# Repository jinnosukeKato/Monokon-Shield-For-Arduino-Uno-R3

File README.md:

# Monokon-Shield for Arduino Uno R3

ものづくりコンテスト制御の対象基板、制作基盤と Arduino Uno R3 を接続するためのシールドです

[KiCad 6.0](https://www.kicad.org/) 用のデータです  
ガーバーファイルとドリルファイルを出力して、基板メーカ等に発注するなりしてください

## 特徴

- Arduino Uno R3 と同寸法
- デバッグ用LED搭載
- 一層基板

## 使いかた

この基盤をArduino Unoに差し込み、CN3に制作基盤(当日制作する基板)を接続し、CN1, CN2に制御対象基板を接続してください。

## 必要な部品

- [330Ω 抵抗器](https://akizukidenshi.com/catalog/g/gR-25331/) x3
- [10kΩ 抵抗器](https://akizukidenshi.com/catalog/g/gR-25103/) x3
- [C1815 トランジスタ](https://akizukidenshi.com/catalog/g/gI-06475/) x3
- [お好きな色のLED](https://akizukidenshi.com/catalog/g/gI-11333/) x3
- [10ピン ボックスヘッダ](https://akizukidenshi.com/catalog/g/gC-12664/) x2
- [2.54mm ピンヘッダ](https://akizukidenshi.com/catalog/g/gC-00167/)

## 組み立て上の注意点

- ランドが少し小さいです
- J1-4はピンが裏を向くように実装してください
- トランジスタの足は、ランドに適切に刺さるよう曲げてください
- CN1, CN2のフラットケーブルが交差してしまう配線になっています
- CN1, CN2が参考画像では10ピンヘッダになっていますが、ボックスヘッダを実装することをオススメします
- CN1, CN2にボックスヘッダを実装する場合は▼がLED側に来るように実装してください
- シルクに`神奈川工業高校 ものづくり同好会`と入ってます

## ピン対応表

| Arduinoのピン | 接続先 | メモ |
| --- | --- | --- |
| 0 | NC | - |
| 1 | NC | - |
| 2 | 7セグ左ON/OFF | - |
| 3 | 7セグ右ON/OFF | - |
| 4 | ブザー | tone()で鳴らしてください |
| 5 | クロック | DCモーター/ステッピングモーター使用時に入力必須 |
| 6 | 7セグ/ステッピング | 7セグのピンは一番上の横棒から時計回り |
| 7 | 7セグ/ステッピング | - |
| 8 | 7セグ/ステッピング | - |
| 9 | 7セグ/ステッピング | - |
| 10 | 7セグ/DCモーター | - |
| 11 | 7セグ/DCモーター | - |
| 12 | 7セグ | 中央横棒 |
| 13 | 7セグ | 小数点 |
| 14 | 製作基盤入力 | digitalRead用 |
| 15 | 製作基盤入力 | digitalRead用 |
| 16 | 製作基盤入力 | digitalRead用 |
| A0 | 製作基盤入力 | AnalogRead用 |
| A1 | 製作基盤入力 | AnalogRead用 |
| A2 | 製作基盤入力 | AnalogRead用 |

## Special Thanks

- K先輩(Arduino MEGA用の基盤データ提供、LEDの回路を参考にさせてもらいました)
- 神奈川工業高校ものづくり同好会

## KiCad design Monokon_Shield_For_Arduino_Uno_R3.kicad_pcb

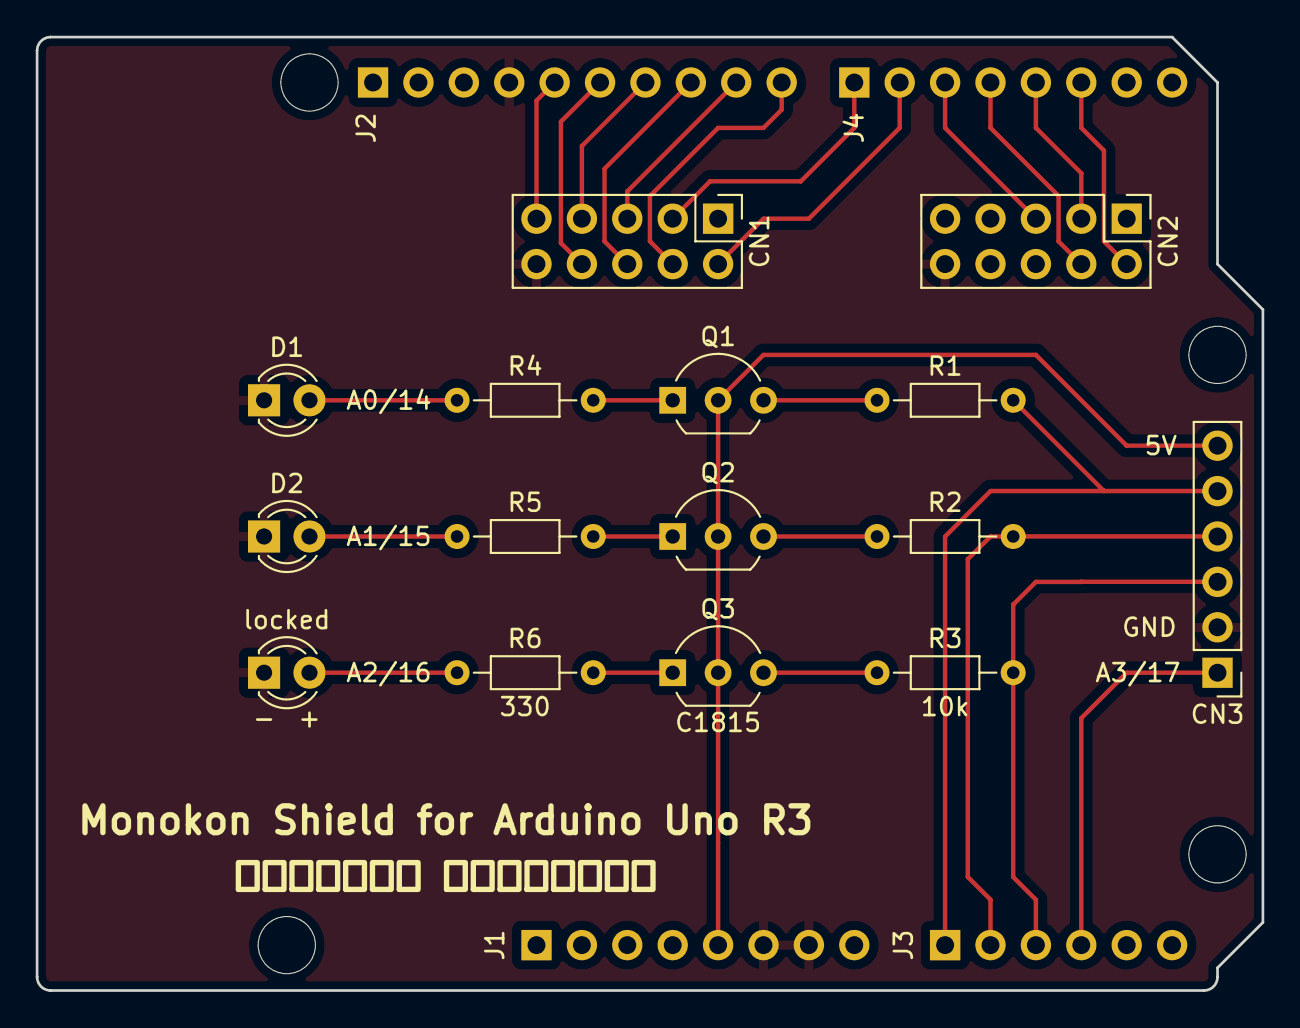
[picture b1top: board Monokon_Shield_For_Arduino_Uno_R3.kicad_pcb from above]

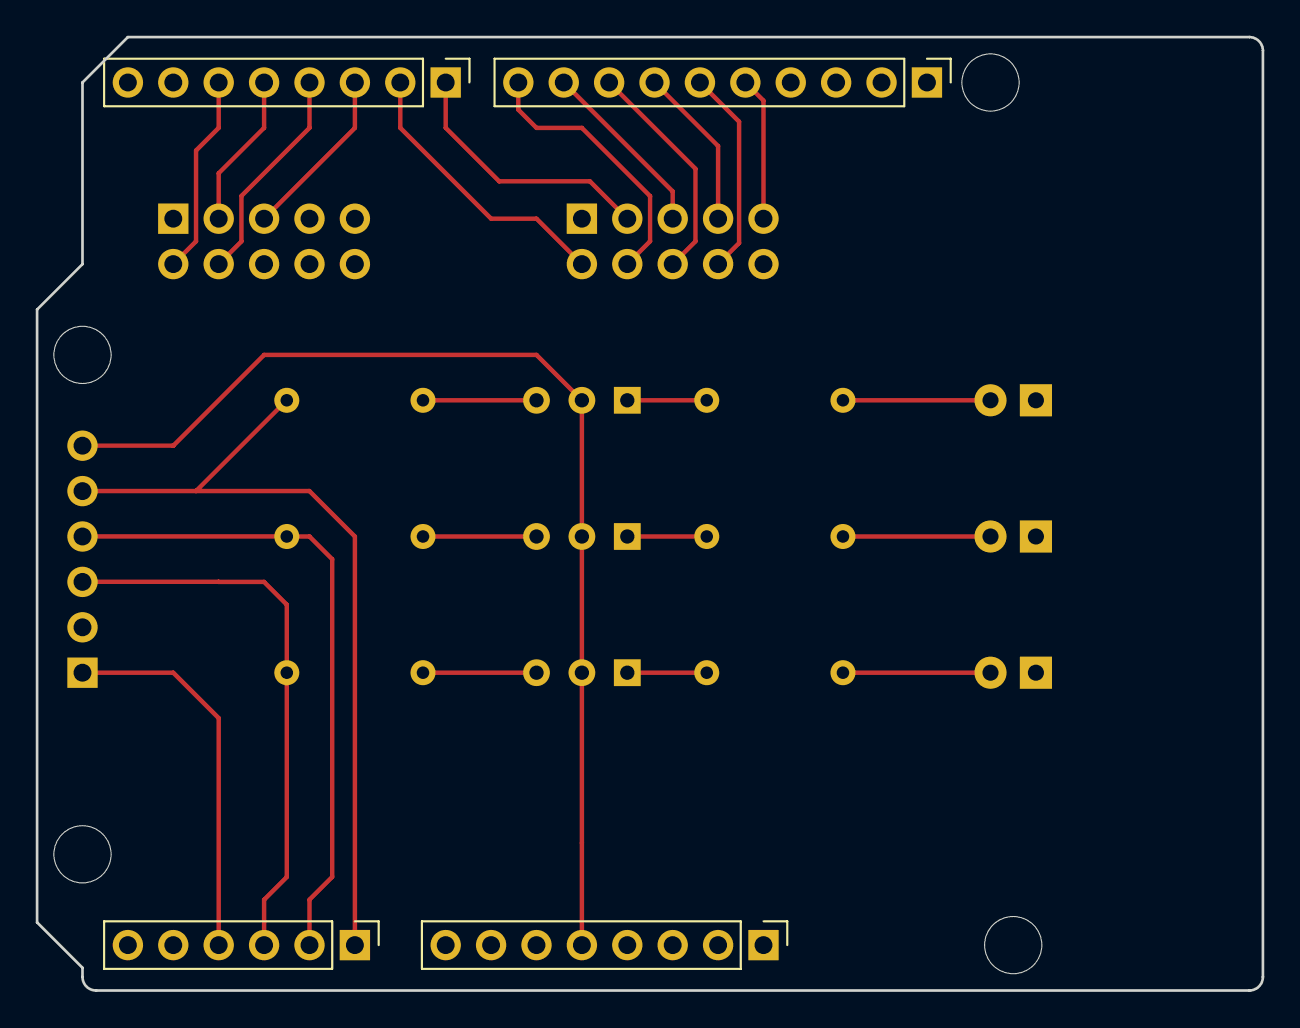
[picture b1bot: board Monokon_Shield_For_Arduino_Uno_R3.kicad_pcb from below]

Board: 2 copper layers, 68.6 x 53.3 mm, 23 parts (4 on the bottom side), 27 nets.

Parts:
CN1, CN2: 2x5 10-Pin Male Box Header; PinHeader_2x05_P2.54mm_Vertical
CN3: 6-Pin Headers; PinHeader_1x06_P2.54mm_Vertical
D1, D2: LED; LED_D3.0mm
J1: locked; PinHeader_1x08_P2.54mm_Vertical
J2: Digital/PWM; PinHeader_1x10_P2.54mm_Vertical
J3: Analog; PinHeader_1x06_P2.54mm_Vertical
J4: Digital/PWM; PinHeader_1x08_P2.54mm_Vertical
MH1, MH2, MH3, MH4: MountingHole_3.2mm
Q1, Q2, Q3: C1815; TO-92_Inline_Wide
R1, R2, R3: 10k; R_Axial_DIN0204_L3.6mm_D1.6mm_P7.62mm_Horizontal
R4, R5, R6: 330; R_Axial_DIN0204_L3.6mm_D1.6mm_P7.62mm_Horizontal
locked: LED; LED_D3.0mm

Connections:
2: CN2.2, J4.6
3: CN2.3, J4.5
4: CN2.4, J4.4
5: CN2.5, J4.3
6: CN1.2, J4.2
7: CN1.3, J4.1
8: CN1.4, J2.10
9: CN1.5, J2.9
10: CN1.6, J2.8
11: CN1.7, J2.7
12: CN1.8, J2.6
13: CN1.9, J2.5
+5V: CN3.6, J1.5, Q1.2 (C), Q2.2 (C), Q3.2 (C)
A0: CN3.5, J3.1, R1.1
A1: CN3.4, J3.2, R2.1
A2: CN3.3, J3.3, R3.1
A3: CN3.1, J3.4
GND: CN1.10, CN2.10, CN3.2, D1.1 (K), D2.1 (K), J1.6, J1.7, J2.4, locked.1 (K)
unnamed: D1.2 (A), R4.2
unnamed: D2.2 (A), R5.2
unnamed: R6.2, locked.2 (A)
unnamed: Q1.1 (E), R4.1
unnamed: Q1.3 (B), R1.2
unnamed: Q2.1 (E), R5.1
unnamed: Q2.3 (B), R2.2
unnamed: Q3.1 (E), R6.1
unnamed: Q3.3 (B), R3.2

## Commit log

2022-11-04 v1.1
2022-11-04 シルクの部品名を修正
2022-11-04 参考画像を追加
2022-11-04 ライセンスを追加
2022-11-04 readmeを追加
2022-11-08 ピンの対応表を追記
2022-12-04 組み立てて気づいたことを追記
2022-12-27 readme気になったから修正
